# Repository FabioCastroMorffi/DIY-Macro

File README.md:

# DIY-Macro

DIY-Macro is a 3x3 macropad with a rotary encoder and an OLED display. It was designed as a Starter Project during the Highway event in Hackclub.

## BOM

* 8x White DSA Keycaps
* 8x Cherry MX Switches
* 9x 1N4148 Diodes
* 1x XIAO RP2040 micro-controller
* 4x M3x16mm Screw Bolt
* 4x M3x5x4mm Heatset Inserts
* 1x 0.91 inch OLED display
* 1x EC11 Rotary Encoder
* 1x PCB
* 1x Case(divided into top and bottom, 3d printed)

## Schematic

## PCB

Something to improve in the future would definitely be **track placement** when routing. As the amount of components increases, effective routing becomes essential!

## CAD Model

The model is very similar to the standard one from Hackpad. The case is held in place with 4 heatset inserts that hold the top and the bottom together. My main struggle relied on matching the openings for the top and the bottom together for all components. Having two instances of the top helped me with this due to being able to update the top and directly check whether it matched the pcb and the bottom.

The model was done in Fusion 360 (in the browser unfortunately)

## Layers and Top View

## Firmware

The firmware is done with the kmk library in Python and I will troubleshoot(if necessary) upon the receiving of the kit. 

## Thank you

To the Hackclub Team leading this event, thank you so much for the opportunity. This introduction to hardware has expanded my views on technology and given me the opportunity get a taste of hardware design. I'm truly grateful for that.

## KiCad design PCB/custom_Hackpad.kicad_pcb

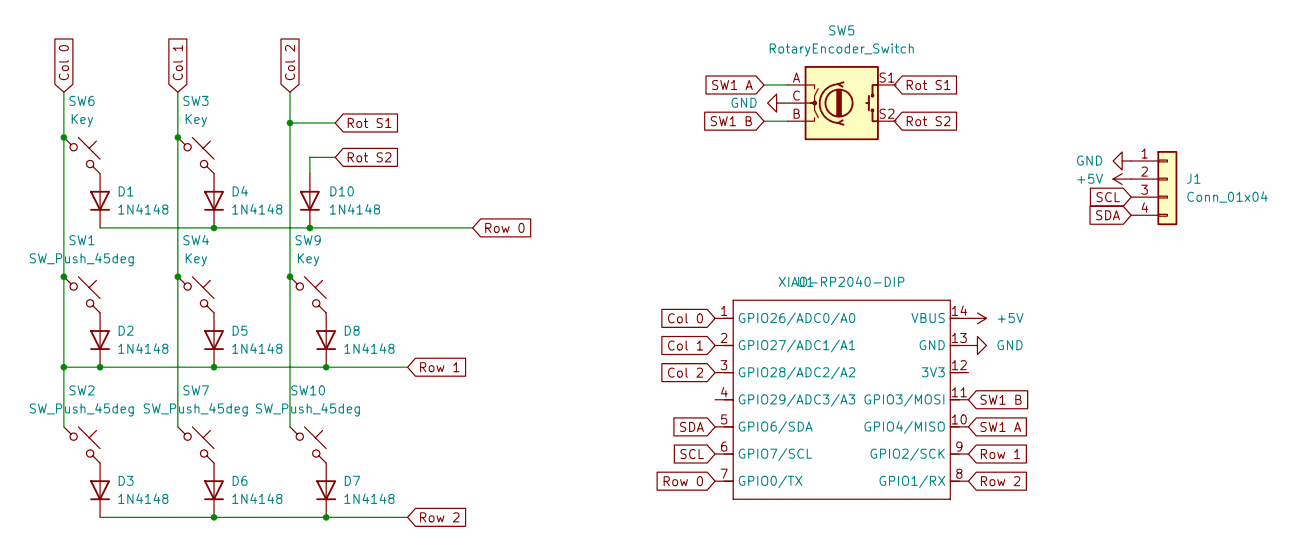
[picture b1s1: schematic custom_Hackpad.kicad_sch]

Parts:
D1, D2, D3, D4, D5, D6, D7, D8, D10: 1N4148; D_DO-35_SOD27_P7.62mm_Horizontal
J1: Conn_01x04; SSD1306-0.91-OLED-4pin-128x32
SW1, SW2, SW7, SW10: SW_Push_45deg; MX_KeySwitch 3D
SW3, SW4, SW6, SW9: Key; MX_KeySwitch 3D
SW5: RotaryEncoder_Switch; RotaryEncoder_Alps_EC11E-Switch_Vertical_H20mm
U1: XIAO-RP2040-DIP

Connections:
+5V: J1.2, U1.14 (VBUS)
Col 0: D2.1 (K), D5.1 (K), D8.1 (K), SW1.1, SW2.1, SW6.1, U1.1 (GPIO26/ADC0/A0), U1.9 (GPIO2/SCK)
Col 1: SW3.1, SW4.1, SW7.1, U1.2 (GPIO27/ADC1/A1)
Col 2: SW5.S1, SW9.1, SW10.1, U1.3 (GPIO28/ADC2/A2); also elsewhere on the board
GND: J1.1, SW5.C, U1.13 (GND)
unnamed: D1.2 (A), SW6.2
unnamed: D2.2 (A), SW1.2
unnamed: D3.2 (A), SW2.2
unnamed: D4.2 (A), SW3.2
unnamed: D5.2 (A), SW4.2
unnamed: D6.2 (A), SW7.2
unnamed: D7.2 (A), SW10.2
unnamed: D8.2 (A), SW9.2
Rot S2: D10.2 (A), SW5.S2
Row 0: D1.1 (K), D4.1 (K), D10.1 (K), U1.7 (GPIO0/TX)
Row 2: D3.1 (K), D6.1 (K), D7.1 (K), U1.8 (GPIO1/RX)
SCL: J1.3, U1.6 (GPIO7/SCL)
SDA: J1.4, U1.5 (GPIO6/SDA)
SW1 A: SW5.A, U1.10 (GPIO4/MISO)
SW1 B: SW5.B, U1.11 (GPIO3/MOSI)

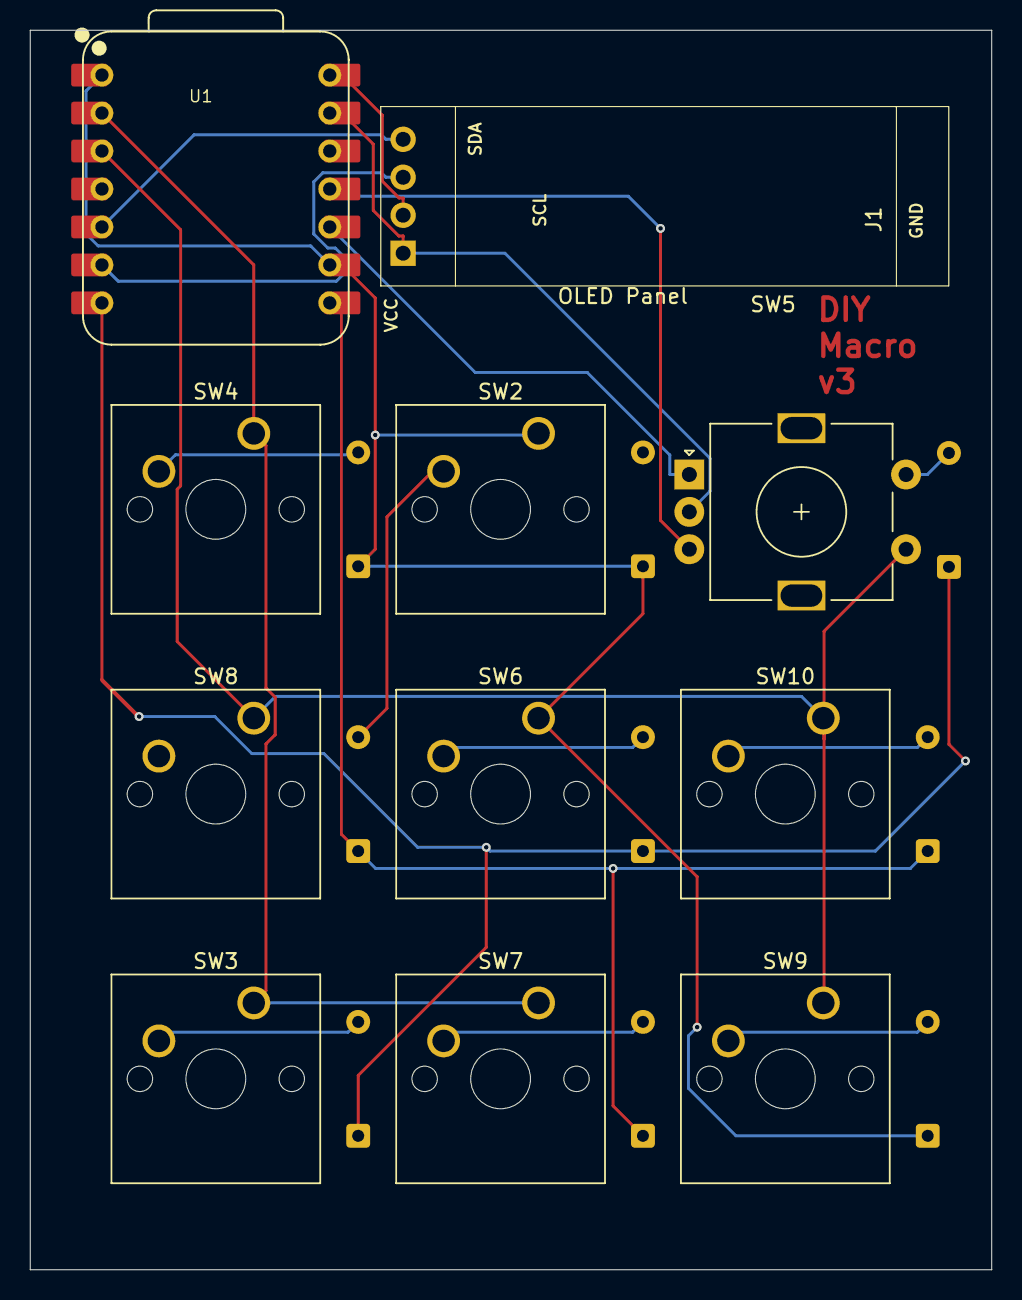
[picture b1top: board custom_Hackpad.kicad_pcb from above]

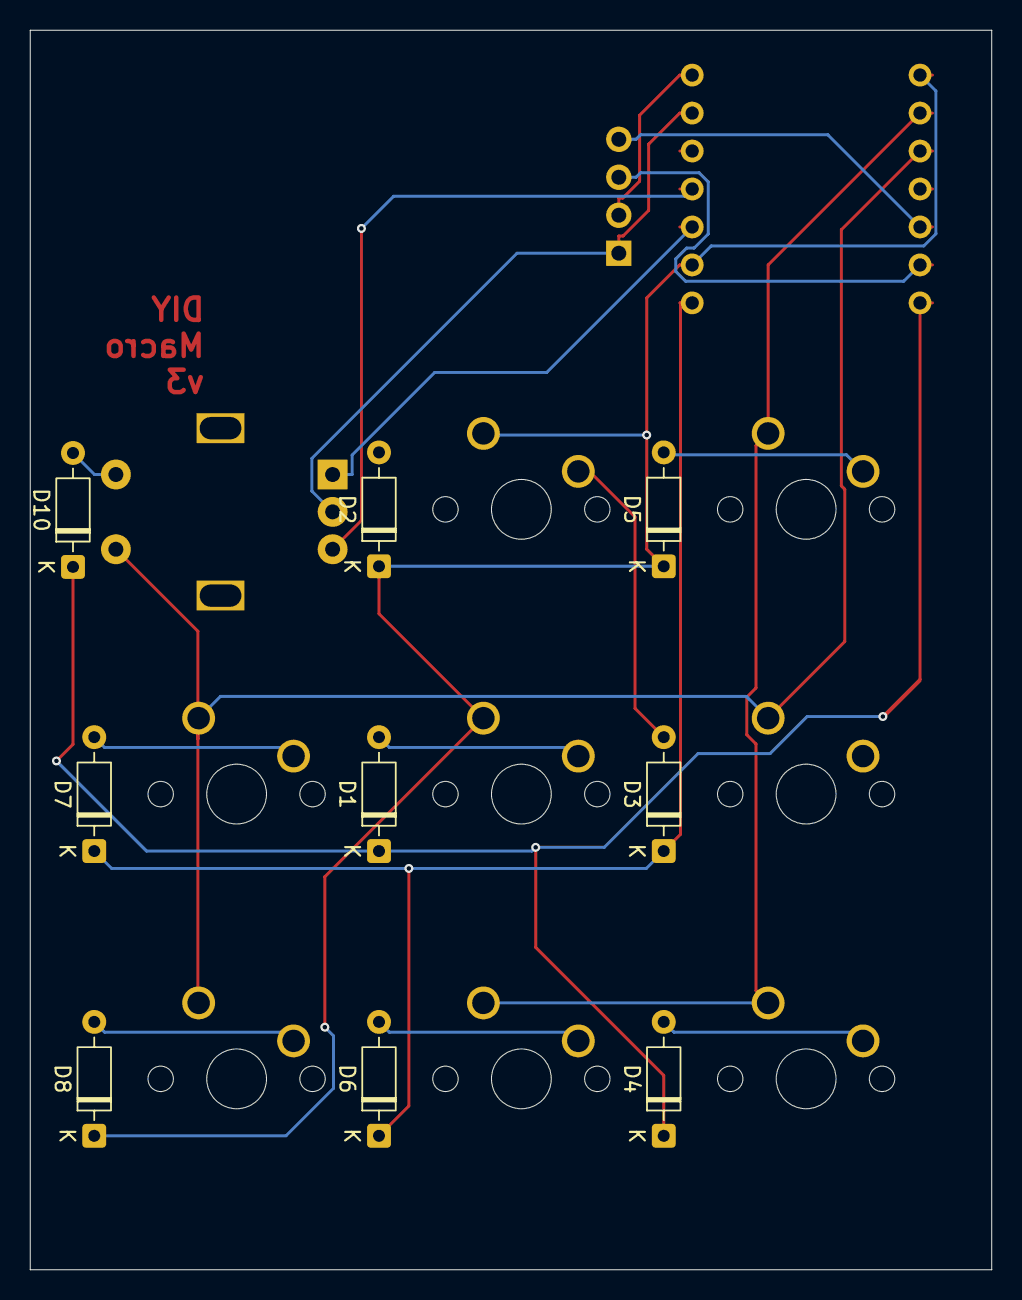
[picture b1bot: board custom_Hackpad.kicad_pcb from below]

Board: 2 copper layers, 64.3 x 82.9 mm, 20 parts (9 on the bottom side), 19 nets.

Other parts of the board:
SW8: Key; MX_KeySwitch 3D

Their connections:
Col 2: SW8.1; also elsewhere on the board

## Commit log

2025-06-04 initial folders
2025-06-04 added firmware python file
2025-06-04 adding files
2025-06-04 test png
2025-06-04 adding more pngs
2025-06-04 replacing pngs
2025-06-04 change pngs
2025-06-04 more pngs
